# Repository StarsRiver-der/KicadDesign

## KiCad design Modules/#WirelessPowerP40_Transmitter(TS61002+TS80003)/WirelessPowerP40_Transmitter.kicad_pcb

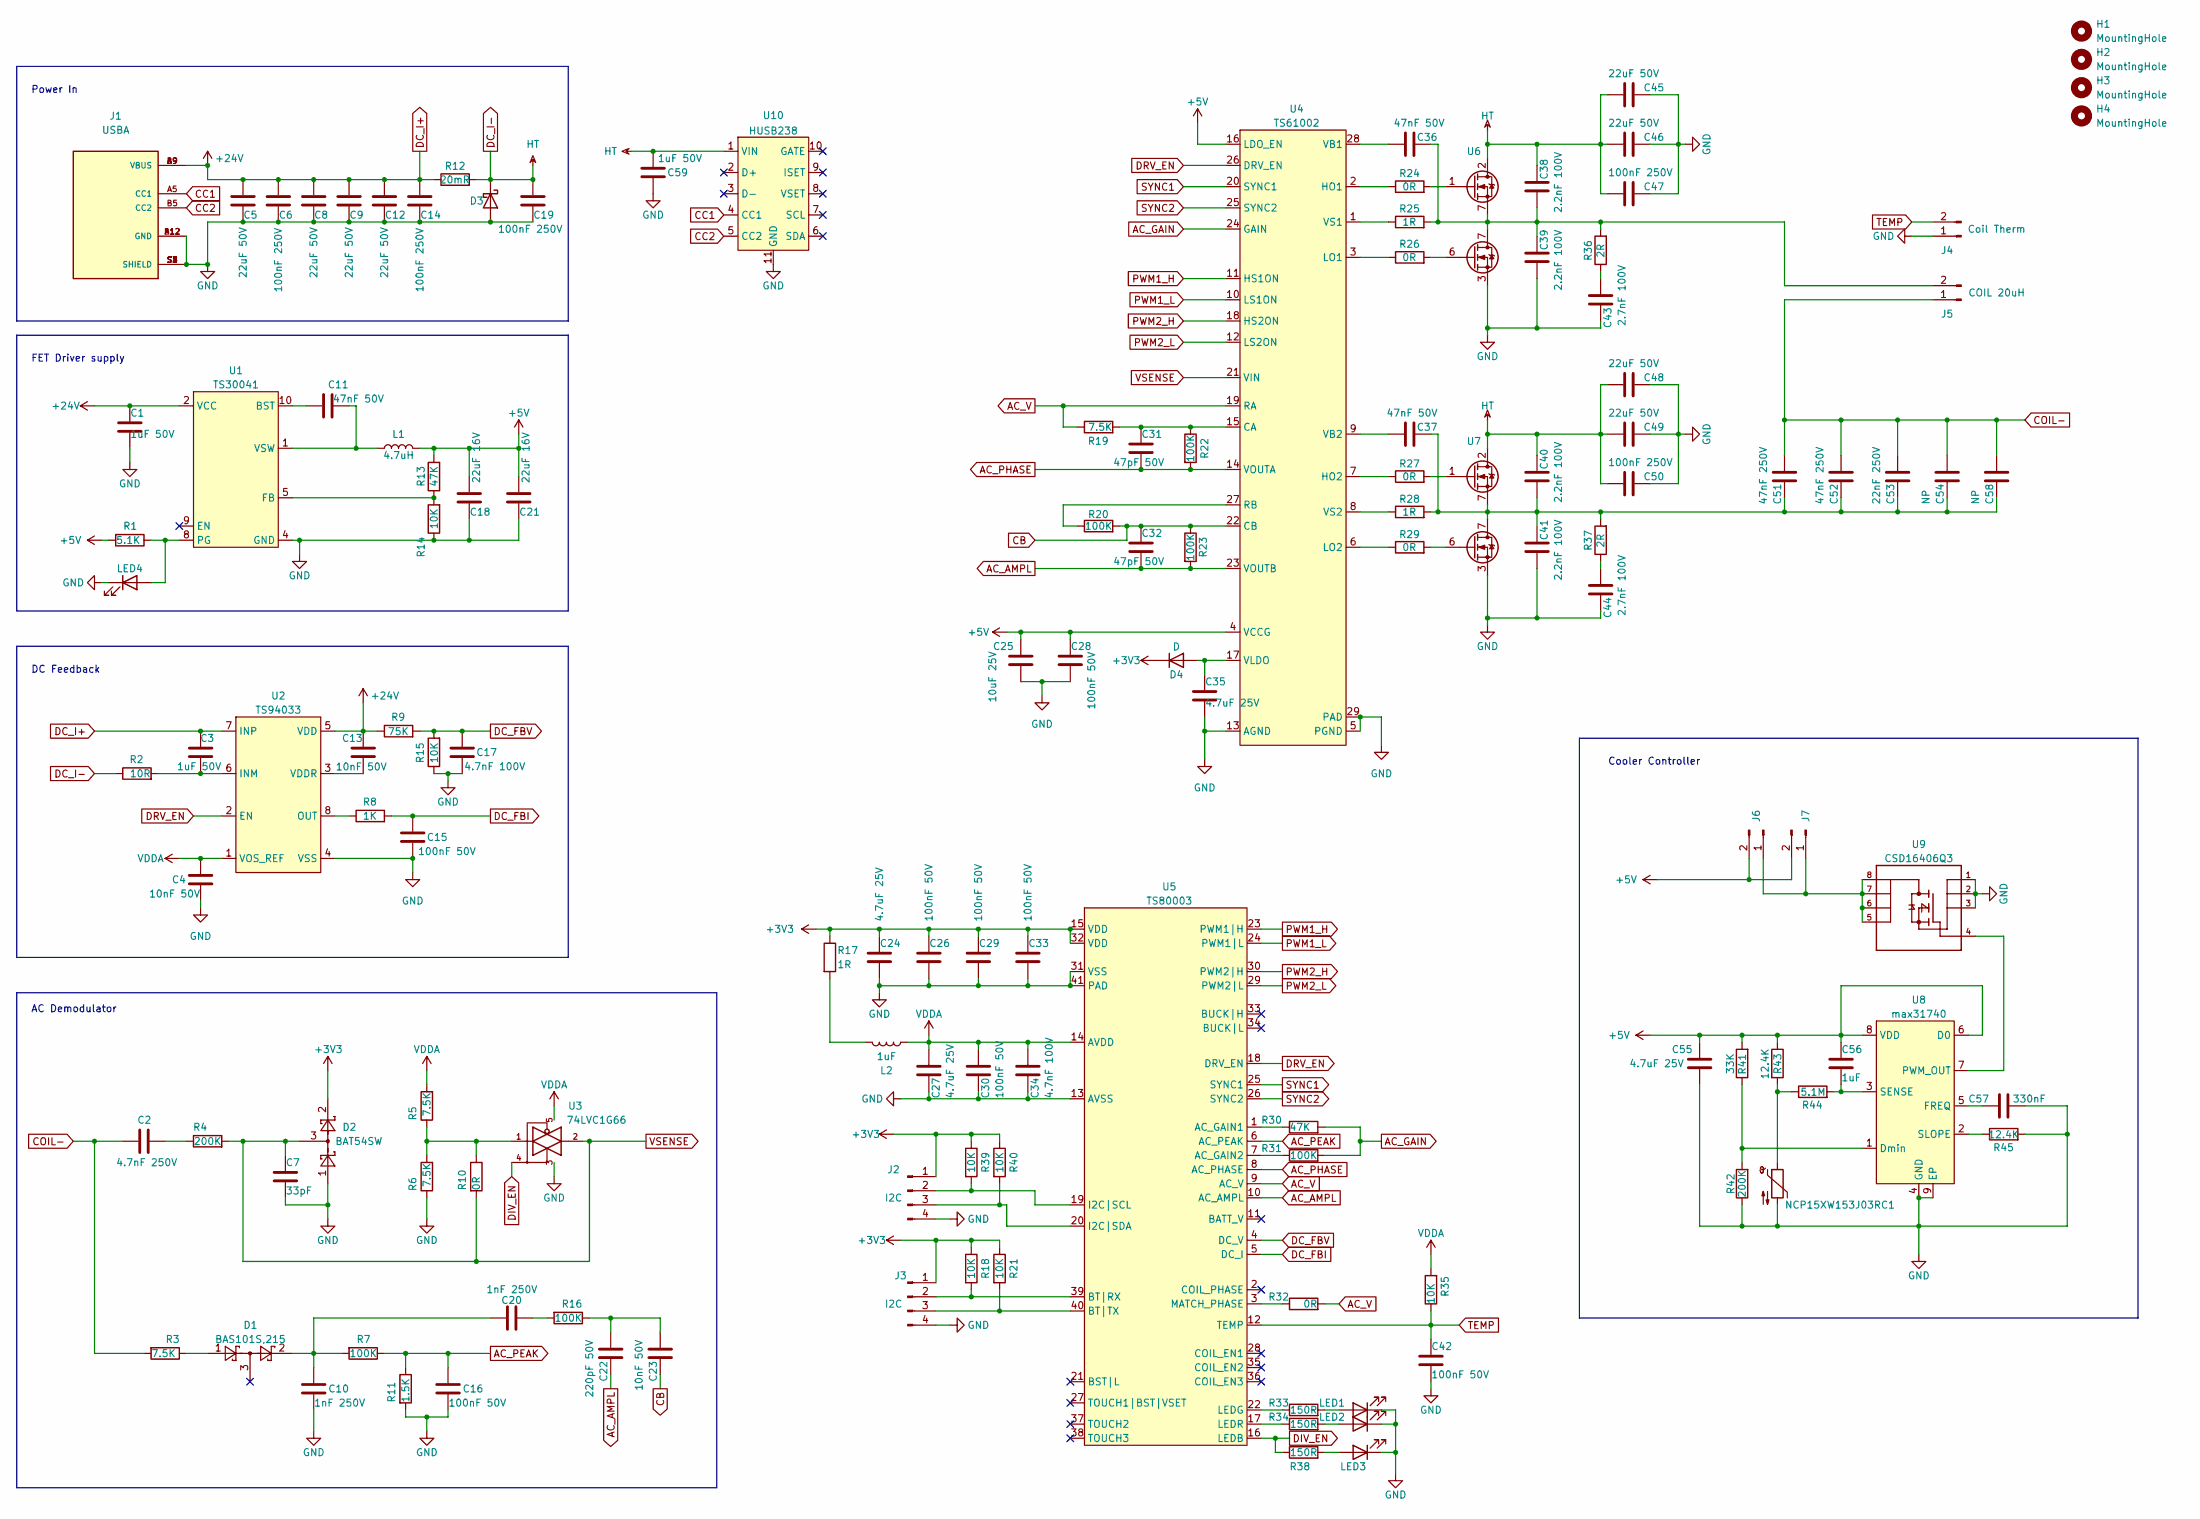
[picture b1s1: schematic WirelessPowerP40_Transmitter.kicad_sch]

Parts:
C1, C3, C59: 1uF 50V; C_0402_1005Metric
C2: 4.7nF 250V; C_0603_1608Metric
C4, C13, C23: 10nF 50V; C_0402_1005Metric
C5, C8, C9, C12, C45, C46, C48, C49: 22uF 50V; C_0805_2012Metric
C6, C14, C19, C47, C50: 100nF 250V; C_0805_2012Metric
C7: 33pF; C_0402_1005Metric
C10, C20: 1nF 250V; C_0603_1608Metric
C11, C36, C37: 47nF 50V; C_0402_1005Metric
C15, C16, C26, C28, C29, C30, C33, C42: 100nF 50V; C_0402_1005Metric
C17, C34: 4.7nF 100V; C_0402_1005Metric
C18, C21: 22uF 16V; C_0603_1608Metric
C22: 220pF 50V; C_0402_1005Metric
C24, C27, C35, C55: 4.7uF 25V; C_0402_1005Metric
C25: 10uF 25V; C_0603_1608Metric
C31, C32: 47pF 50V; C_0402_1005Metric
C38, C39, C40, C41: 2.2nF 100V; C_0805_2012Metric
C43, C44: 2.7nF 100V; C_0805_2012Metric
C51, C52: 47nF 250V; C_1210_3225Metric
C53: 22nF 250V; C_1210_3225Metric
C54, C58: NP; C_1210_3225Metric
C56: 1uF; C_0402_1005Metric
C57: 330nF; C_0402_1005Metric
D1: BAS101S,215; SOT-23
D2: BAT54SW; SOT-323_SC-70
D3: BZT52C30 30V; D_0805_2012Metric
D4: D; D_SOD-523
H1, H2, H3, H4: MountingHole; MountingHole_2.2mm_M2_Pad_Via
J1: USBA; USB4125-GF-A_REVA2; PARTREV Rev A2
J2, J3: I2C; PinHeader_1x04_P2.00mm_Vertical
J4: Coil Therm; PinHeader_1x02_P2.00mm_Vertical
J5: COIL 20uH; AMASS_XT30U-F_1x02_P5.0mm_Vertical
J6, J7: Conn_01x02_Male; PinHeader_1x02_P2.00mm_Vertical
L1: 4.7uH; L_Wuerth_HCI-5040
L2: 1uF; L_Taiyo-Yuden_NR-30xx
LED1, LED2, LED3, LED4: LED; LED_0402_1005Metric
NCP15XW153J03RC1: Thermistor_NTC; R_0402_1005Metric
R1: 5.1K; R_0402_1005Metric
R2: 10R; R_0402_1005Metric
R3, R5, R6, R19: 7.5K; R_0402_1005Metric
R4, R42: 200K; R_0402_1005Metric
R7, R16: 100K; R_0603_1608Metric
R8: 1K; R_0402_1005Metric
R9: 75K; R_0402_1005Metric
R10, R24, R26, R27, R29, R32: 0R; R_0402_1005Metric
R11: 1.5K; R_0402_1005Metric
R12: 20mR; R_2512_6332Metric
R13, R30: 47K; R_0402_1005Metric
R14, R15, R18, R21, R35, R39, R40: 10K; R_0402_1005Metric
R17, R25, R28: 1R; R_0402_1005Metric
R20, R22, R23, R31: 100K; R_0402_1005Metric
R33, R34, R38: 150R; R_0402_1005Metric
R36, R37: 2R; R_0805_2012Metric
R41: 33K; R_0402_1005Metric
R43, R45: 12.4K; R_0402_1005Metric
R44: 5.1M; R_0402_1005Metric
U1: TS30041; QFN-16-1EP_3x3mm_P0.5mm_EP1.7x1.7mm
U2: TS94033; SOT-23-8
U3: 74LVC1G66; SOT-353_SC-70-5
U4: TS61002; QFN-28-1EP_5x5mm_P0.5mm_EP3.35x3.35mm
U5: TS80003; QFN-40-1EP_5x5mm_P0.4mm_EP3.6x3.6mm
U6, U7: BSC0993ND; Infineon_PG-TISON-8-2
U8: max31740; TDFN-8-1EP_3x2mm_P0.5mm_EP1.80x1.65mm
U9: CSD16406Q3
U10: HUSB238; DFN-10-1EP_3x3mm_P0.5mm_EP1.65x2.38mm

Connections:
+3V3: C24.1, C26.1, C29.1, C33.1, D2.2, D4.1 (K), J2.1, J3.1, R17.1, R18.1, R21.1, R39.1, R40.1, U5.15 (VDD), U5.32 (VDD)
+5V: C18.1, C21.1, C25.1, C28.1, C55.1, C56.1, J6.2, J7.2, L1.2, R1.2, R13.2, R41.2, R43.1, U4.4 (VCCG), U4.16 (LDO_EN), U8.6 (D0), U8.8 (VDD)
AC_AMPL: C22.1, C32.2, R23.2, U4.23 (VOUTB), U5.10 (AC_AMPL)
AC_GAIN: R30.2, R31.2, U4.24 (GAIN)
AC_PEAK: C16.1, R7.1, R11.1, U5.6 (AC_PEAK)
AC_PHASE: C31.2, R22.2, U4.14 (VOUTA), U5.8 (AC_PHASE)
AC_V: R19.1, R32.2, U4.19 (RA), U5.9 (AC_V)
CB: C23.1, C32.1, R20.2, R23.1, U4.22 (CB)
CC1: J1.A5 (CC1), U10.4 (CC1)
CC2: J1.B5 (CC2), U10.5 (CC2)
COIL-: C2.2, C51.1, C52.1, C53.1, C54.1, C58.1, J5.1, R3.2
DC_FBI: C15.2, R8.2, U5.5 (DC_I)
DC_FBV: C17.2, R9.2, R15.2, U5.4 (DC_V)
DC_I+: C1.1, C3.2, C5.1, C6.1, C8.1, C9.1, C12.1, C13.2, C14.1, J1.A9 (VBUS), J1.B9 (VBUS), R9.1, R12.1, U1.2 (VCC), U1.3 (VCC), U1.11 (VCC), U2.5 (VDD), U2.7 (INP)
DC_I-: C19.1, C38.2, C40.2, C45.2, C46.2, C47.2, C48.2, C49.2, C50.2, C59.2, D3.1 (K), R2.1, R12.2, U6.2, U7.2, U10.1 (VIN)
DIV_EN: R38.1, U3.4, U5.16 (LEDB)
DRV_EN: U2.2 (EN), U4.26 (DRV_EN), U5.18 (DRV_EN)
GND: C1.2, C4.1, C5.2, C6.2, C7.2, C8.2, C9.2, C10.2, C12.2, C14.2, C15.1, C16.2, C17.1, C18.2, C19.2, C21.2, C24.2, C25.2, C26.2, C27.2, C28.2, C29.2, C30.2, C33.2, C34.2, C35.2, C39.1, C41.1, C42.2, C43.1, C44.1, C45.1, C46.1, C47.1, C48.1, C49.1, C50.1, C55.2, C57.2, C59.1, D2.1, D3.2 (A), J1.A12 (GND), J1.B12 (GND), J1.S1 (SHIELD), J1.S2 (SHIELD), J1.S3 (SHIELD), J1.S4 (SHIELD), J2.4, J3.4, J4.1, LED1.1 (K), LED2.1 (K), LED3.1 (K), LED4.1 (K), NCP15XW153J03RC1.2, R6.1, R11.2, R14.1, R15.1, R42.1, R45.2, U1.4 (GND), U1.14 (GND), U1.15 (GND), U1.17 (GND), U2.4 (VSS), U3.3, U4.5 (PGND), U4.13 (AGND), U4.29 (PAD), U5.13 (AVSS), U5.31 (VSS), U5.41 (PAD), U6.3, U6.4, U6.5, U7.3, U7.4, U7.5, U8.4 (GND), U8.9 (EP), U9.1, U9.2, U9.3, U10.11 (GND)
unnamed: C2.1, R4.1
unnamed: C3.1, R2.2, U2.6 (INM)
unnamed: C10.1, C20.1, D1.2, R7.2
unnamed: C11.1, U1.10 (BST)
unnamed: C11.2, L1.1, U1.1 (VSW), U1.12 (VSW), U1.13 (VSW), U1.16 (VSW)
unnamed: C13.1, U2.3 (VDDR)
unnamed: C20.2, R16.2
unnamed: C22.2, C23.2, R16.1
unnamed: C31.1, R19.2, R22.1, U4.15 (CA)
unnamed: C35.1, D4.2 (A), U4.17 (VLDO)
unnamed: C36.1, U4.28 (VB1)
unnamed: C36.2, C38.1, C39.2, J5.2, R25.2, R36.2, U6.7
unnamed: C37.1, U4.9 (VB2)
unnamed: C37.2, C40.1, C41.2, C51.2, C52.2, C53.2, C54.2, C58.2, R28.2, R37.2, U7.7
unnamed: C43.2, R36.1
unnamed: C44.2, R37.1
unnamed: C56.2, R44.2, U8.3 (SENSE)
unnamed: C57.1, U8.5 (FREQ)
unnamed: D1.1, R3.1
unnamed: J2.2, R39.2, U5.19 (I2C|SCL)
unnamed: J2.3, R40.2, U5.20 (I2C|SDA)
unnamed: J3.2, R18.2, U5.39 (BT|RX)
unnamed: J3.3, R21.2, U5.40 (BT|TX)
unnamed: J6.1, J7.1, U9.5, U9.6, U9.7, U9.8
unnamed: L2.2, R17.2
unnamed: LED1.2 (A), R34.2
unnamed: LED2.2 (A), R33.2
unnamed: LED3.2 (A), R38.2
unnamed: LED4.2 (A), R1.1, U1.8 (PG)
unnamed: NCP15XW153J03RC1.1, R43.2, R44.1
unnamed: R8.1, U2.8 (OUT)
unnamed: R5.1, R6.2, R10.1, U3.1
unnamed: R13.1, R14.2, U1.5 (FB)
unnamed: R20.1, U4.27 (RB)
unnamed: R24.1, U4.2 (HO1)
unnamed: R24.2, U6.1
unnamed: R25.1, U4.1 (VS1)
unnamed: R26.1, U4.3 (LO1)
unnamed: R26.2, U6.6
unnamed: R27.1, U4.7 (HO2)
unnamed: R27.2, U7.1
unnamed: R28.1, U4.8 (VS2)
unnamed: R29.1, U4.6 (LO2)
unnamed: R29.2, U7.6
unnamed: R30.1, U5.1 (AC_GAIN1)
unnamed: R31.1, U5.7 (AC_GAIN2)
unnamed: R32.1, U5.3 (MATCH_PHASE)
unnamed: R33.1, U5.22 (LEDG)
unnamed: R34.1, U5.17 (LEDR)
unnamed: R41.1, R42.2, U8.1 (Dmin)
unnamed: R45.1, U8.2 (SLOPE)
unnamed: U8.7 (PWM_OUT), U9.4
PWM1_H: U4.11 (HS1ON), U5.23 (PWM1|H)
PWM1_L: U4.10 (LS1ON), U5.24 (PWM1|L)
PWM2_H: U4.18 (HS2ON), U5.30 (PWM2|H)
PWM2_L: U4.12 (LS2ON), U5.29 (PWM2|L)
SYNC1: U4.20 (SYNC1), U5.25 (SYNC1)
SYNC2: U4.25 (SYNC2), U5.26 (SYNC2)
TEMP: C42.1, J4.2, R35.1, U5.12 (TEMP)
VDDA: C4.2, C27.1, C30.1, C34.1, L2.1, R5.2, R35.2, U2.1 (VOS_REF), U3.5, U5.14 (AVDD)
VSENSE: C7.1, D2.3, R4.2, R10.2, U3.2, U4.21 (VIN)

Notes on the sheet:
Power In
Cooler Controller
AC Demodulator
DC Feedback
FET Driver supply

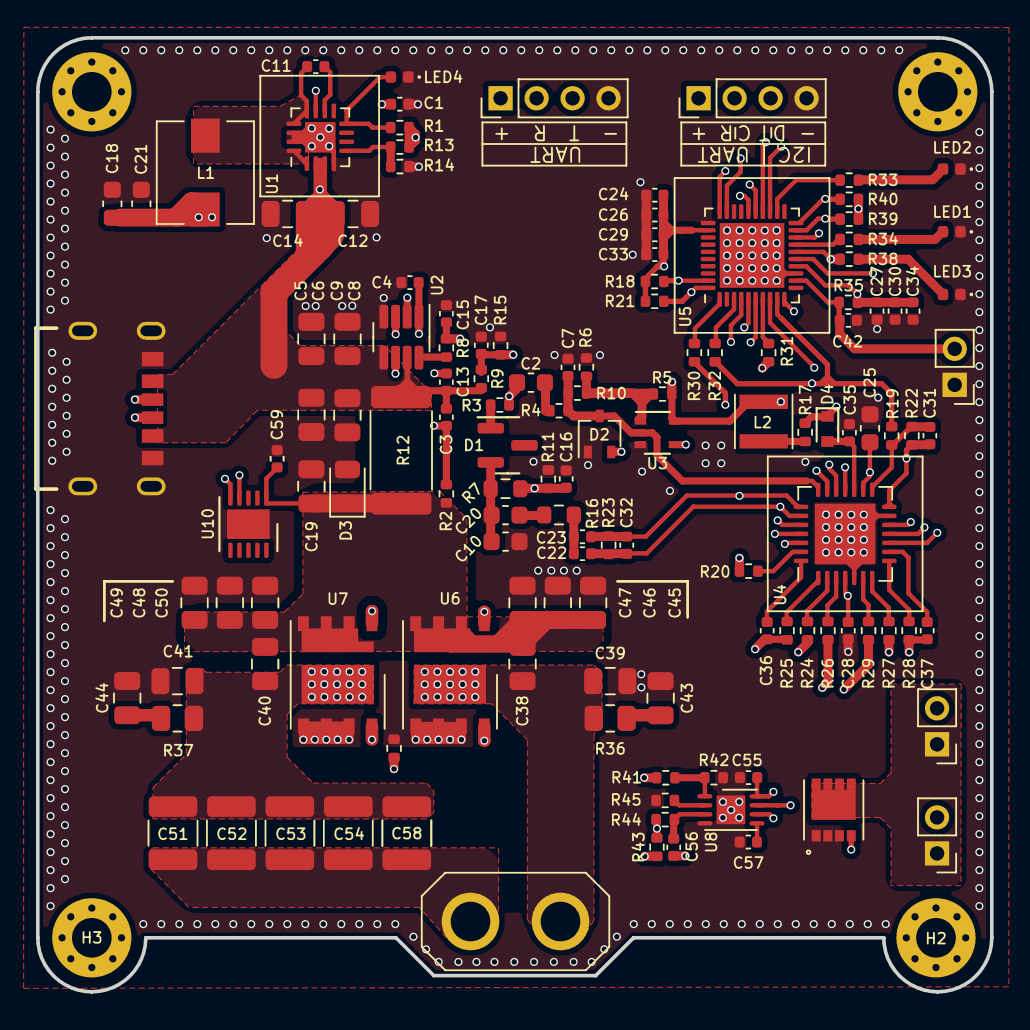
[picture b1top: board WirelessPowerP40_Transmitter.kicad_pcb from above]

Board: 4 copper layers, 53.0 x 53.0 mm, 136 parts (0 on the bottom side), 79 nets.

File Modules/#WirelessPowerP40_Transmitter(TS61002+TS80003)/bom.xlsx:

标号 | 数/板 | 值 | 类型 | 封装 | 数量 | 单价 | 总价
C1, C3 | 2 | 1uF 50V | C | 0402 | 50 | 0 | 0
C2 | 1 | 4.7nF 250V | C | 0603 | 50 | 0 | 0
C4, C13, C23 | 3 | 10nF 50V | C | 0402 | 50 | 0 | 0
C5, C8, C9, C12, C45, C46, C48, C49 | 8 | 22uF 50V | C | 0805 | 50 | 0 | 0
C6, C14, C19, C47, C50 | 5 | 100nF 250V | C | 0805 | 50 | 0 | 0
C7 | 1 | 33pF 100V | C | 0402 | 50 | 0 | 0
C10, C20 | 2 | 1nF 250V | C | 0603 | 50 | 0 | 0
C11, C36, C37 | 3 | 47nF 50V | C | 0402 | 50 | 0 | 0
C15, C16, C26, C28, C29, C30, C33, C42 | 8 | 100nF 50V | C | 0402 | 50 | 0 | 0
C17, C34 | 2 | 4.7nF 100V | C | 0402 | 50 | 0 | 0
C18, C21 | 2 | 22uF 16V | C | 0603 | 50 | 0 | 0
C22 | 1 | 220pF 50V | C | 0402 | 50 | 0 | 0
C24, C27, C35 | 3 | 4.7uF 25V | C | 0402 | 50 | 0 | 0
C25 | 1 | 10uF 25V | C | 0603 | 50 | 0 | 0
C31, C32 | 2 | 47pF 50V | C | 0402 | 50 | 0 | 0
C38, C39, C40, C41 | 4 | 2.2nF 100V | C | 0805 | 50 | 0 | 0
C43, C44 | 2 | 2.7nF 100V | C | 0805 | 50 | 0 | 0
C51, C52 | 2 | 47nF 250V | C | 1210 | 50 | 0 | 0
C53 | 1 | 22nF 250V | C | 1210 | 50 | 0 | 0
C55 | 1 | 4.7uF | C | 0402 | 50 | 0 | 0
C56 | 1 | 1uF | C | 0402 | 50 | 0 | 0
C57 | 1 | 330nF | C | 0402 | 50 | 0 | 0
R1 | 1 | 5.1K | R | 0402 | 50 | 0 | 0
R2 | 1 | 10R | R | 0402 | 50 | 0 | 0
R3, R5, R6, R19 | 4 | 7.5K | R | 0402 | 50 | 0 | 0
R4, R42 | 2 | 200K | R | 0402 | 50 | 0 | 0
R7, R16 | 2 | 100K | R | 0603 | 50 | 0 | 0
R8 | 1 | 1K | R | 0402 | 50 | 0 | 0
R9 | 1 | 75K | R | 0402 | 50 | 0 | 0
R10, R24, R26, R27, R29, R32 | 6 | 0R | R | 0402 | 50 | 0 | 0
R11 | 1 | 1.5K | R | 0402 | 50 | 0 | 0
R12 | 1 | 20mR 1W | R | 2512 | 50 | 0 | 0
R13, R30 | 2 | 47K | R | 0402 | 50 | 0 | 0
R14, R15, R18, R21, R35, R39, R40 | 7 | 10K | R | 0402 | 50 | 0 | 0
R17, R25, R28 | 3 | 1R | R | 0402 | 50 | 0 | 0
R20, R22, R23, R31 | 4 | 100K | R | 0402 | 50 | 0 | 0
R33, R34, R38 | 3 | 150R | R | 0402 | 50 | 0 | 0
R36, R37 | 2 | 2R | R | 0805 | 50 | 0 | 0
R41 | 1 | 33K | R | 0402 | 50 | 0 | 0
R43, R45 | 2 | 12.4K | R | 0402 | 50 | 0 | 0
R44 | 1 | 5.1M | R | 0402 | 50 | 0 | 0
L2 | 1 | 0.6uH | L | 3015 | 10 | 0 | 0
LED1 | 4 | LED 红 | LED | 0402 | 50 | 0 | 0
LED2 | 4 | LED 蓝 | LED | 0402 | 50 | 0 | 0
LED3, LED4 | 4 | LED 翠绿 | LED | 0402 | 50 | 0 | 0
NCP15XW153J03RC1 | 1 | NCP15XW153J03RC1 | 热敏电阻 | 0402 | 10 | 0 | 0
D1 | 1 | BAS101S,215 | BAS101S | SOT-23 | 10 | 0 | 0
D3 | 1 | BZT52C30S | 稳压二极管 | 0805 | 50 | 0 | 0
D1, D2 | 2 | BAT54SW | BAT54SW | SOT-323_SC-70 | 10 | 0 | 0
U1 | 1 | TS30041 |  | QFN-16-1EP_3x3mm_P0.5mm_EP1.7x1.7mm | 1 | 0 | 0
U2 | 1 | TS94033 |  | SOT-23-8 | 1 | 0 | 0
U3 | 1 | 74LVC1G66 |  | TSSOP5 | 1 | 0 | 0
U4 | 1 | TS61002 |  | QFN-28-1EP_5x5mm_P0.5mm_EP3.35x3.35mm | 1 | 0 | 0
U5 | 1 | TS80003 |  | QFN-40-1EP_5x5mm_P0.4mm_EP3.6x3.6mm | 1 | 0 | 0
U6, U7 | 2 | BSC0993ND |  | Infineon_PG-TISON-8-2 | 1 | 0 | 0
U8 | 1 | max31740 |  | TDFN-8-1EP_3x2mm_P0.5mm_EP1.80x1.65mm | 1 | 0 | 0

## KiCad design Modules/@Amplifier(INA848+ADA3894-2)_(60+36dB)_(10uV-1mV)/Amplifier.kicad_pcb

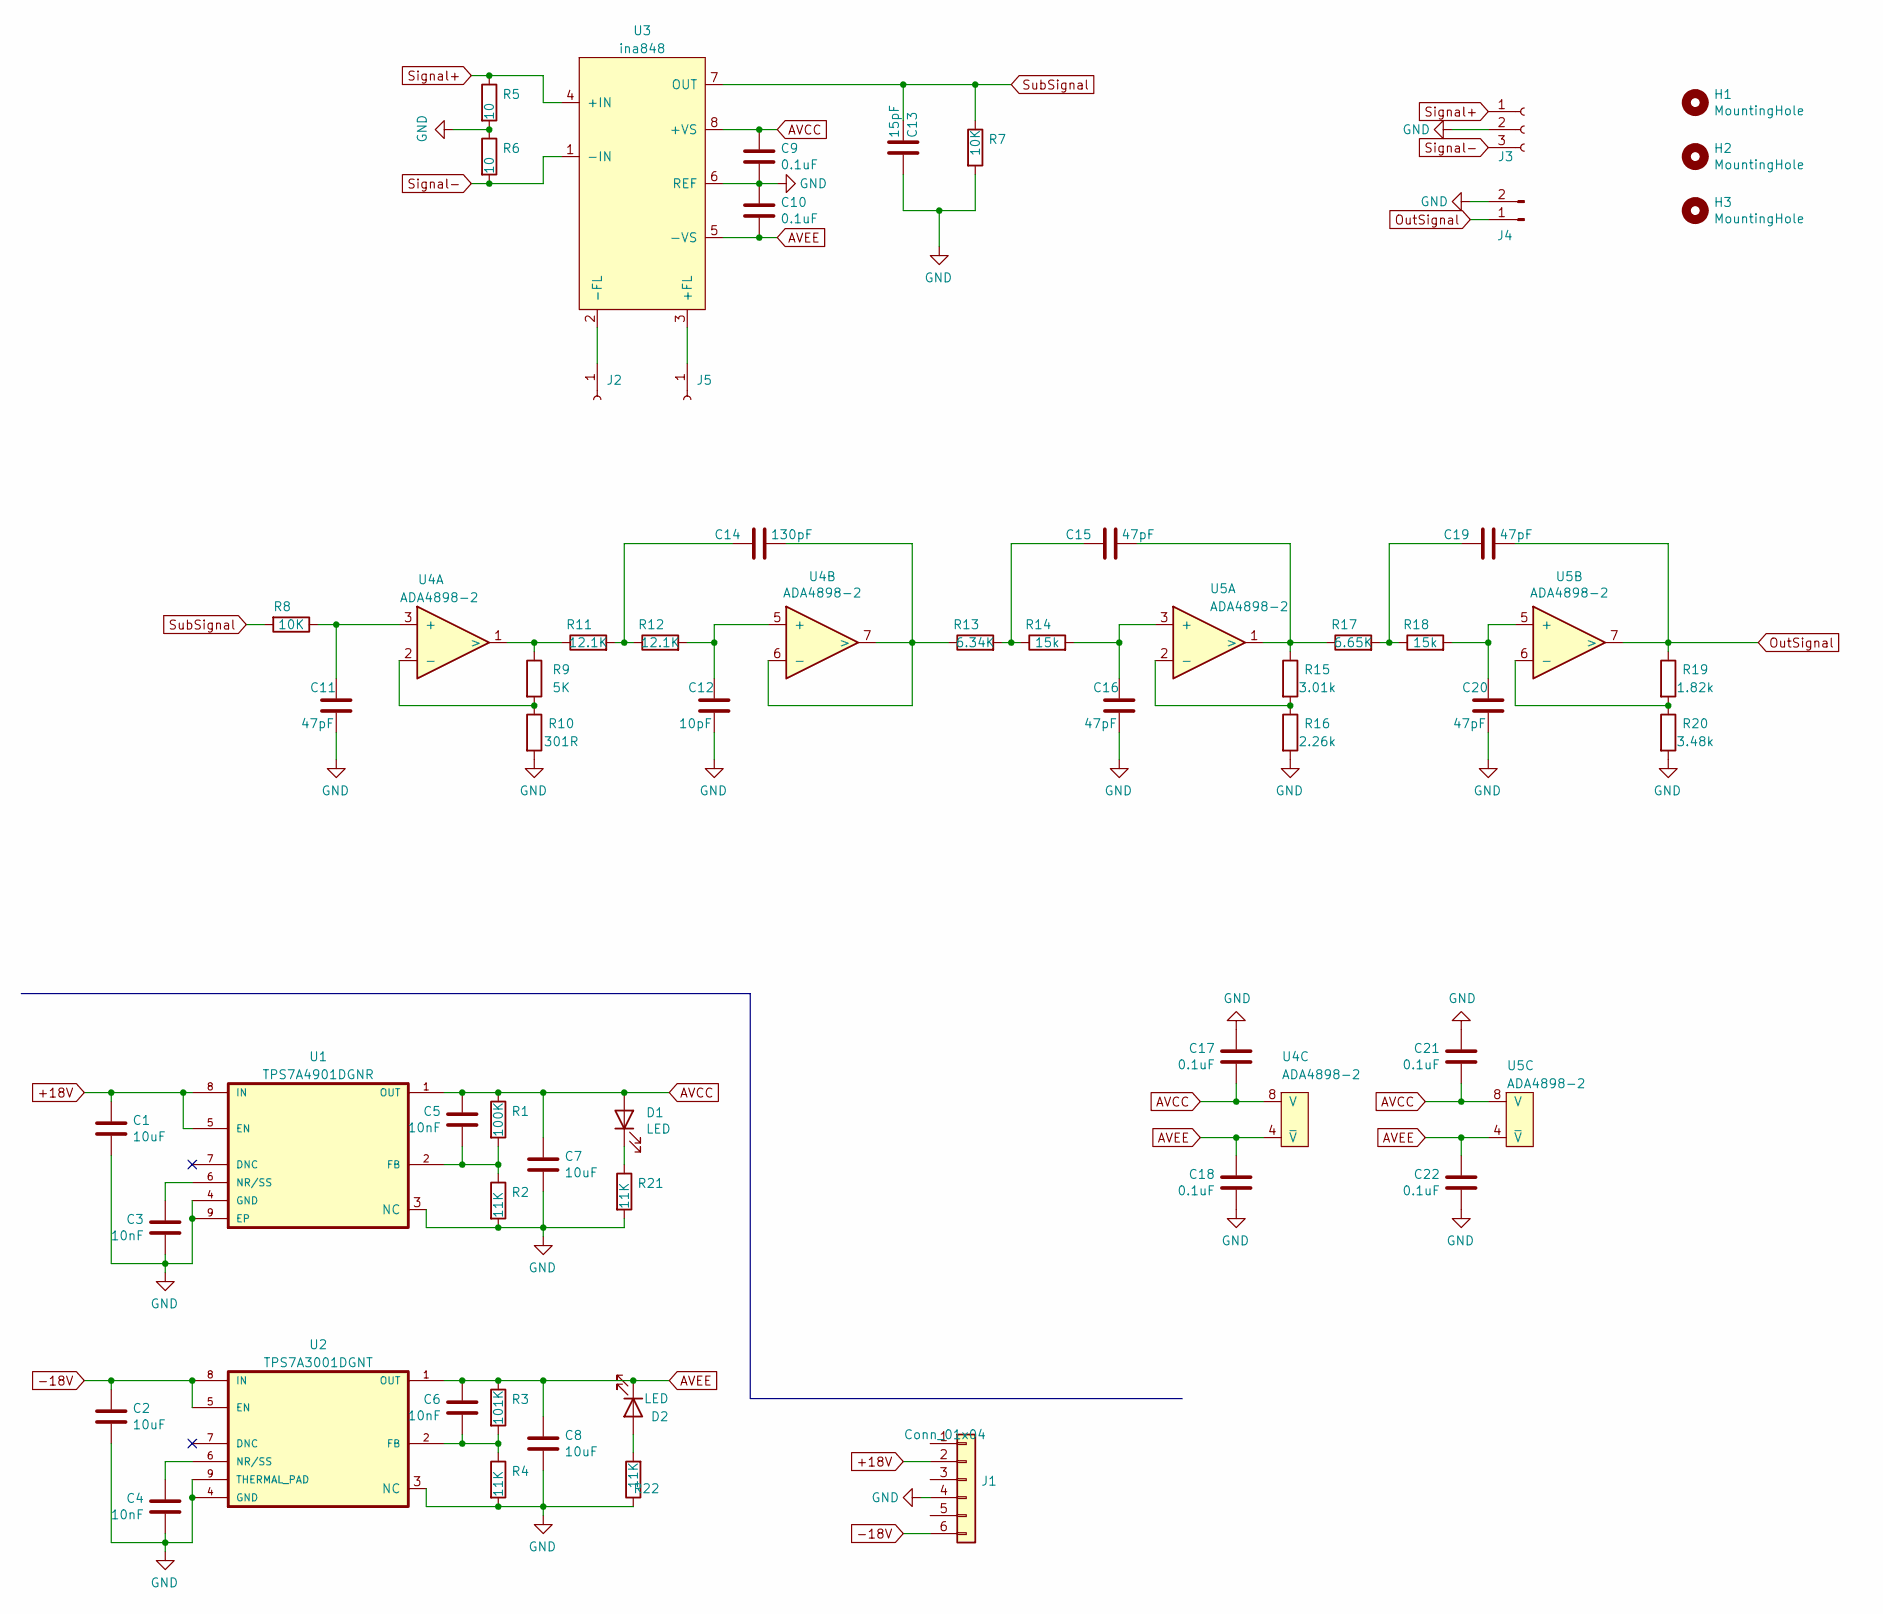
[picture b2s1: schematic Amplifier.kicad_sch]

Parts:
C1, C2, C7, C8: 10uF; C_0603_1608Metric
C3, C4, C5, C6: 10nF; C_0402_1005Metric
C9, C10, C17, C18, C21, C22: 0.1uF; C_1206_3216Metric
C11, C15, C16, C19, C20: 47pF; C_0402_1005Metric
C12: 10pF; C_0402_1005Metric
C13: 15pF; C_0402_1005Metric
C14: 130pF; C_0402_1005Metric
D1, D2: LED; LED_0402_1005Metric
H1, H2, H3: MountingHole; MountingHole_2.2mm_M2
J1: Conn_01x04; Multicomp_MC9A12-1034_2x03_P2.54mm_Vertical
J2, J5: Conn_01x01_Female; MountingPad_1mm
J3: Conn_01x03_Female; PinSocket_1x03_P2.54mm_Vertical
J4: Conn_01x02_Male; SMA_Amphenol_132134_Vertical
R1: 100K; R_0402_1005Metric
R2, R4, R21, R22: 11K; R_0402_1005Metric
R3: 101K; R_0402_1005Metric
R5, R6: 10; R_0402_1005Metric
R7, R8: 10K; R_0402_1005Metric
R9: 5K; R_0402_1005Metric
R10: 301R; R_0402_1005Metric
R11, R12: 12.1K; R_0402_1005Metric
R13: 6.34K; R_0402_1005Metric
R14, R18: 15k; R_0402_1005Metric
R15: 3.01k; R_0402_1005Metric
R16: 2.26k; R_0402_1005Metric
R17: 6.65K; R_0402_1005Metric
R19: 1.82k; R_0402_1005Metric
R20: 3.48k; R_0402_1005Metric
U1: TPS7A4901DGNR; SOP65P490X110-9N
U2: TPS7A3001DGNT; SOP65P490X110-9N
U3: ina848; SOIC-8_3.9x4.9mm_P1.27mm
U4, U5: ADA4898-2; SOIC-8-1EP_3.9x4.9mm_P1.27mm_EP2.29x3mm

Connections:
+18V: C1.1, J1.2, U1.5 (EN), U1.8 (IN)
-18V: C2.1, J1.6, U2.5 (EN), U2.8 (IN)
AVCC: C5.1, C7.1, C9.1, C17.2, C21.2, D1.2 (A), R1.1, U1.1 (OUT), U3.8 (+VS), U4.8 (V), U5.8 (V)
AVEE: C6.1, C8.1, C10.2, C18.1, C22.1, D2.1 (K), R3.1, U2.1 (OUT), U3.5 (-VS), U4.4 (~V), U5.4 (~V)
GND: C1.2, C2.2, C3.2, C4.2, C7.2, C8.2, C9.2, C10.1, C11.2, C12.2, C13.2, C16.2, C17.1, C18.2, C20.2, C21.1, C22.2, J1.4, J3.2, J4.2, R2.2, R4.2, R5.2, R6.1, R7.2, R10.2, R16.2, R20.2, R21.2, R22.1, U1.3 (NC), U1.4 (GND), U1.9 (EP), U2.3 (NC), U2.4 (GND), U2.9 (THERMAL_PAD), U3.6 (REF)
unnamed: C3.1, U1.6 (NR/SS)
unnamed: C4.1, U2.6 (NR/SS)
unnamed: C5.2, R1.2, R2.1, U1.2 (FB)
unnamed: C6.2, R3.2, R4.1, U2.2 (FB)
unnamed: C11.1, R8.1, U4.3 (+)
unnamed: C12.1, R12.2, U4.5 (+)
unnamed: C14.1, R11.2, R12.1
unnamed: C14.2, R13.1, U4.6 (-), U4.7 (>)
unnamed: C15.1, R13.2, R14.1
unnamed: C15.2, R15.1, R17.1, U5.1 (>)
unnamed: C16.1, R14.2, U5.3 (+)
unnamed: C19.1, R17.2, R18.1
unnamed: C20.1, R18.2, U5.5 (+)
unnamed: D1.1 (K), R21.1
unnamed: D2.2 (A), R22.2
unnamed: J2.1, U3.2 (-FL)
unnamed: J5.1, U3.3 (+FL)
unnamed: R9.2, R10.1, U4.2 (-)
unnamed: R9.1, R11.1, U4.1 (>)
unnamed: R15.2, R16.1, U5.2 (-)
unnamed: R19.2, R20.1, U5.6 (-)
OutSignal: C19.2, J4.1, R19.1, U5.7 (>)
Signal+: J3.1, R5.1, U3.4 (+IN)
Signal-: J3.3, R6.2, U3.1 (-IN)
SubSignal: C13.1, R7.1, R8.2, U3.7 (OUT)

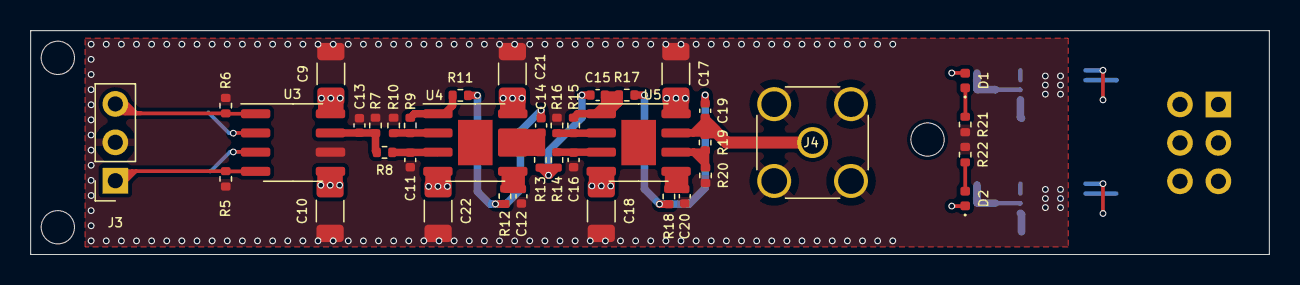
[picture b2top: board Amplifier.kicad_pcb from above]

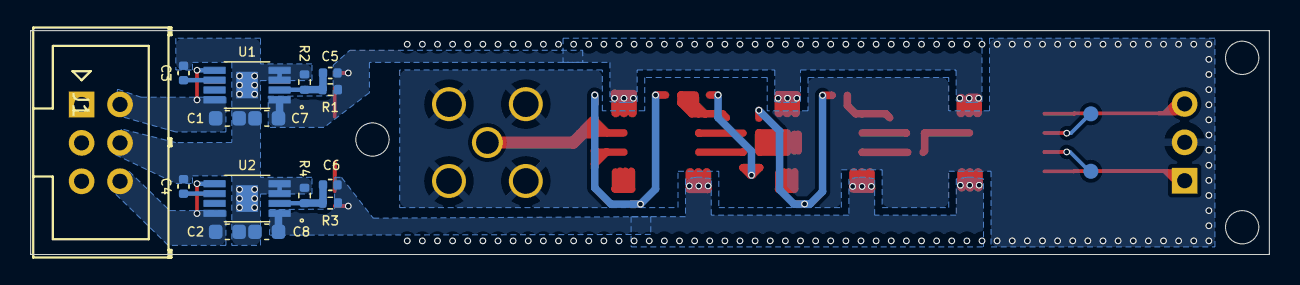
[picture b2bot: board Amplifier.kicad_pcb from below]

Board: 4 copper layers, 81.9 x 14.8 mm, 59 parts (17 on the bottom side), 30 nets.

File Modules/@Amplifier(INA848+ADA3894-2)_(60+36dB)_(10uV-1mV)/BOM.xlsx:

符号 | 数量/板 | 值 | 备注 | 封装 | 数量 | 单价 | 总价
C1, C2, C7, C8 | 4 | 10uF | 25V | 0603 | 100 | 0.1
C3, C4, C5, C6 | 4 | 10nF | 25V | 0402 | 100 | 1.4999999999999999E-2
C9, C10, C17, C18, C21, C22 | 6 | 100nF | 25V COG高频电容 | 1206 | 50
C11, C15, C16, C19, C20 | 5 | 47pF | 25V | 0402 | 100 | 1.4999999999999999E-2
C12 | 1 | 10pF | 25V | 0402 | 100 | 1.4999999999999999E-2
C13 | 1 | 15pF | 25V | 0402 | 100 | 1.4999999999999999E-2
C14 | 1 | 130pF | 25V | 0402 | 100 | 1.4999999999999999E-2
D1, D2 | 2 | LED |  | 0402 | 100
R1 | 1 | 100K |  | 0402 | 100 | 0.01
R2, R4, R21, R22 | 4 | 11K |  | 0402 | 100 | 0.01
R3 | 1 | 101K |  | 0402 | 100 | 0.01
R5, R6 | 2 | 10R |  | 0402 | 100 | 0.01
R7, R8 | 2 | 10K |  | 0402 | 100 | 0.01
R9 | 1 | 5K |  | 0402 | 100 | 0.01
R10 | 1 | 301R |  | 0402 | 100 | 0.01
R11, R12 | 2 | 12.1K |  | 0402 | 100 | 0.01
R13 | 1 | 6.34K |  | 0402 | 100 | 0.01
R14, R18 | 2 | 15k |  | 0402 | 100 | 0.01
R15 | 1 | 3.01k |  | 0402 | 100 | 0.01
R16 | 1 | 2.26k |  | 0402 | 100 | 0.01
R17 | 1 | 6.65K |  | 0402 | 100 | 0.01
R19 | 1 | 1.82k |  | 0402 | 100 | 0.01
R20 | 1 | 3.48k |  | 0402 |  | 0.01
U1 | 1 | TPS7A4901DGNR | TPS7A4901DGNR:TPS7A4901DGNR |  | 5 | 8
U2 | 1 | TPS7A3001DGNT | TPS7A3001DGNT:TPS7A3001DGNT |  | 5 | 8
UX | 1 | ina849 | INA:ina849 | SOIC-8_3.9x4.9mm | 2
U3 | 1 | ina848 | INA:ina848 | SOIC-8_3.9x4.9mm | 2
U4, U5 | 2 | ADA4898-2 | ADA:ADA4898-2 | SOIC-8_3.9x4.9mm | 2

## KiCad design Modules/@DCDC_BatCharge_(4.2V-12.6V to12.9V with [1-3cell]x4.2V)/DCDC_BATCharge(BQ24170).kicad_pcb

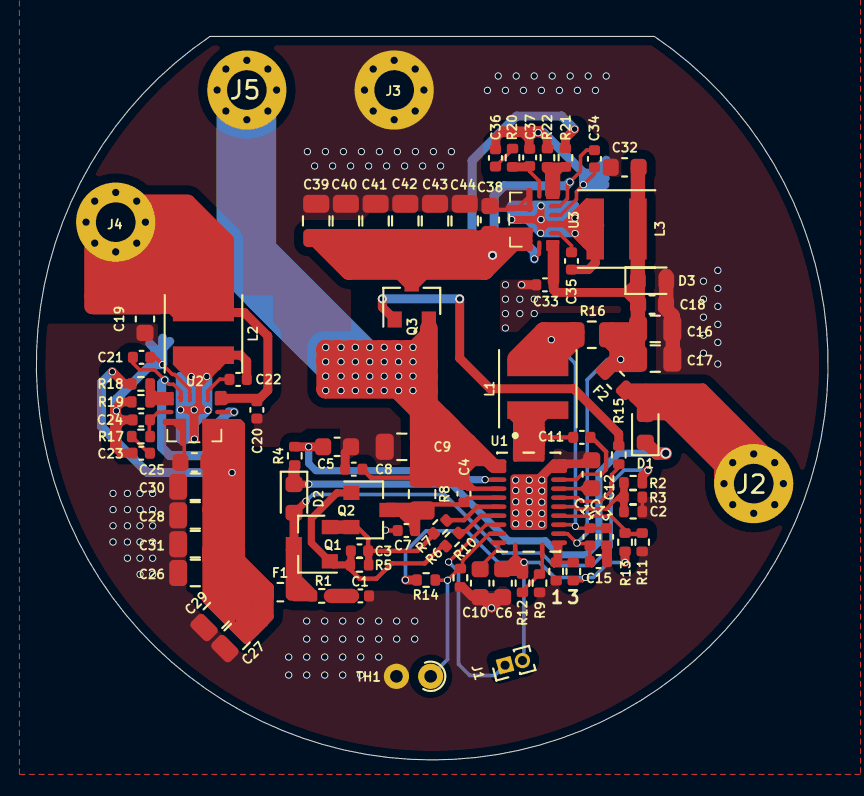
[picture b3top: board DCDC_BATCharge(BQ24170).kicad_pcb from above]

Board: 2 copper layers, 44.0 x 40.2 mm, 88 parts (0 on the bottom side), 42 nets.

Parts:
C1, C21, C34: 2.2uF; C_0402_1005Metric
C2: 330pF; R_0402_1005Metric
C3: 47nF; C_0402_1005Metric
C4, C7, C8, C13, C14, C15, C20, C22, C33, C35: 0.1uF; C_0402_1005Metric
C5, C6, C12: 1uF; C_0603_1608Metric
C9, C16, C17: 10uF; C_0805_2012Metric
C10, C18: 0.1uF; C_0603_1608Metric
C11: 0.047uF; C_0402_1005Metric
C19, C25, C32, C38: 10uF; C_0603_1608Metric
C23, C36: 39nF; C_0402_1005Metric
C24, C37: 100pF; C_0402_1005Metric
C26, C27, C28, C29, C30, C31, C39, C40, C41, C42, C43, C44: 22uF; C_0805_2012Metric
D1, D2, D3: D; D_0603_1608Metric
F1: 3.5A; Fuse_0603_1608Metric
F2: 10A; Fuse_0603_1608Metric
J1: Btn_LED; PinHeader_1x02_P1.00mm_Vertical
J2: VIA_V_PACK; MountingHole_2.2mm_M2_Pad_Via
J3: VIA_GND; MountingHole_2.2mm_M2_Pad_Via
J4: VIA_V_Adapter; MountingHole_2.2mm_M2_Pad_Via
J5: VIA_V_SYS; MountingHole_2.2mm_M2_Pad_Via
L1: 3.3uH CoilCraft 40xx; L_Coilcraft_XxL4020
L2, L3: 1.8uH CoilCraft 40xx; L_Coilcraft_XxL4020
Q1, Q2: AO3416; SOT-23
Q3: AO3415; SOT-23
R1: 2R; R_0402_1005Metric
R2, R18, R21: 1M; R_0402_1005Metric
R3, R13: 100K; R_0402_1005Metric
R4: 10R; R_0402_1005Metric
R5: 500K; R_0402_1005Metric
R6, R7: 4.02K; R_0402_1005Metric
R8, R16: 0.01; R_0805_2012Metric
R9: 32.4K; R_0402_1005Metric
R10: 30.1K; R_0402_1005Metric
R11: 22.1K; R_0402_1005Metric
R12: 232K; R_0402_1005Metric
R14: 5.23K; R_0402_1005Metric
R15: 1K; R_0402_1005Metric
R17, R20: 47.5k; R_0402_1005Metric
R19, R22: 48.7K; R_0402_1005Metric
R_DN1: 0; R_0402_1005Metric
R_UP1: 0; R_0402_1005Metric
TH1: MF52A 10K 3380; R_Axial_DIN0204_L3.6mm_D1.6mm_P1.90mm_Vertical
U1: BQ24170; BQ24170RGYT
U2, U3: TPS61288

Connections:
Adapter: C19.2, C20.2, J4.1, L2.1, U2.7 (VIN)
BQ_Vref: C6.1, J1.2, R12.2, R13.1, R14.1, R_UP1.1, U1.12 (VREF)
Charger: C25.2, C26.2, C27.2, C28.2, C29.2, C30.2, C31.2, F1.1, R18.2, U2.5 (Vout)
GND: C1.1, C2.1, C5.1, C6.2, C7.1, C8.1, C9.1, C10.2, C12.2, C13.1, C15.1, C16.1, C17.1, C18.1, C19.1, C20.1, C21.1, C23.1, C24.1, C25.1, C26.1, C27.1, C28.1, C29.1, C30.1, C31.1, C32.1, C33.1, C34.1, C36.1, C37.1, C38.1, C39.1, C40.1, C41.1, C42.1, C43.1, C44.1, D3.2 (A), J3.1, R3.1, R9.1, R10.2, R11.1, R19.1, R22.1, R_DN1.1, TH1.2, U1.22 (PGND), U1.23 (PGND), U1.25 (EP), U2.3 (PGND), U2.10 (AGND), U3.3 (PGND), U3.10 (AGND)
unnamed: C1.2, R1.1
unnamed: C2.2, R2.1, R3.2, U1.18 (OVPSET)
unnamed: C3.1, Q1.1 (G), Q2.1 (G), R5.1, R6.2
unnamed: C3.2, Q1.2 (S), Q2.2 (S), R5.2, R7.2
unnamed: C4.1, C7.2, Q2.3 (D), R8.2, U1.6 (ACP)
unnamed: C5.2, R4.2, U1.4 (AVCC)
unnamed: C10.1, U1.11 (TTC)
unnamed: C11.1, L1.1, U1.1 (SW), U1.24 (SW)
unnamed: C11.2, U1.21 (BTST)
unnamed: C12.1, U1.20 (REGN)
unnamed: C13.2, C14.2, L1.2, R16.2, U1.16 (SRP)
unnamed: C21.2, U2.6 (EN), U2.11 (VCC)
unnamed: C22.1, U2.8 (BST)
unnamed: C22.2, L2.2, U2.4 (SW), U2.9 (SW)
unnamed: C23.2, R17.1
unnamed: C24.2, R17.2, U2.2 (COMP)
unnamed: C34.2, U3.6 (EN), U3.11 (VCC)
unnamed: C35.1, U3.8 (BST)
unnamed: C35.2, L3.2, U3.4 (SW), U3.9 (SW)
unnamed: C36.2, R20.1
unnamed: C37.2, R20.2, U3.2 (COMP)
unnamed: D1.1 (K), D2.1 (K), R4.1
unnamed: D2.2 (A), F1.2, Q1.3 (D), R1.2, R2.2
unnamed: J1.1, U1.9 (STAT)
unnamed: Q3.1 (G), R15.2
unnamed: R6.1, U1.8 (ACDRV)
unnamed: R7.1, U1.7 (CMSRC)
unnamed: R10.1, R14.2, TH1.1, U1.10 (TS)
unnamed: R11.2, R13.2, U1.17 (ACSET)
unnamed: R9.2, R12.1, U1.13 (ISET)
unnamed: R15.1, U1.19 (~BATDRV)
unnamed: R18.1, R19.2, U2.1 (FB)
unnamed: R21.1, R22.2, U3.1 (FB)
unnamed: R_DN1.2, R_UP1.2, U1.14 (CELL)
V_PACK: D1.2 (A), F2.2, J2.1
V_PACK_BOOST: C38.2, C39.2, C40.2, C41.2, C42.2, C43.2, C44.2, Q3.3 (D), R21.2, U3.5 (Vout)
V_PACK_OUT: C14.1, C15.2, C16.2, C17.2, C18.2, C32.2, C33.2, D3.1 (K), F2.1, L3.1, R16.1, U1.15 (SRN), U3.7 (VIN)
V_sys: C4.2, C8.2, C9.2, J5.1, Q3.2 (S), R8.1, U1.2 (PVCC), U1.3 (PVCC), U1.5 (ACN)
